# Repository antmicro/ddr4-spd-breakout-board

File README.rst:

=======================
DDR4 SPD Breakout Board
=======================

Copyright (c) 2022 `Antmicro <https://www.antmicro.com>`_

.. figure:: img/ddr4-spd-breakout.png

Overview
--------

This repository contains open hardware design files for an experimental breakout board which allows reading the Serial Presence Detect (SPD) data from a 288-pin, JEDEC-compliant DDR4 DIMM module.  

The board includes a FT2232HL USB/UART converter with MPSSE which can read DIMM-content over I2C.
This board can be used with our `SPD Data Reader <https://github.com/antmicro/spd-data-reader>`_ software.

Repository structure
--------------------
The main repository directory contains KiCad PCB project files, a LICENSE and README.
The remaining files are stored in the following directories:

* ``lib`` - contains the component libraries
* ``img`` - contains graphics for this README

License
=======

`Apache-2.0 <LICENSE>`_

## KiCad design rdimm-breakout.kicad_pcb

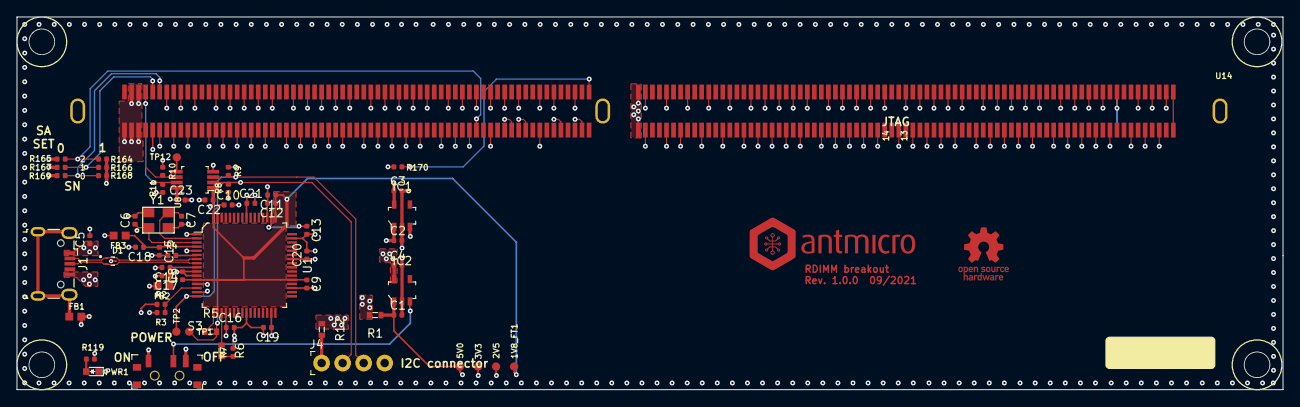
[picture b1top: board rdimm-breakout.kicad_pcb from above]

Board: 4 copper layers, 152.9 x 45.0 mm, 66 parts (0 on the bottom side), 34 nets.

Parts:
1V8_FT1, 2V5, 3V3, 5V0: TP_SMD1MM; Testpoint_smd_1mm
C1, C2, C3, C4: C_1u_0402; 0402-cap
C5, C8, C9, C10, C11, C13, C14, C15, C16, C19, C20, C21, C22, C23: C_100n_0402; 0402-cap
C6, C7: C_27p_0402; 0402-cap
C12, C17, C18: C_4u7_0402; 0402-cap
D1: PESD5V0S2BQA; TPD2E009DRTR
FB1, FB2, FB3: BLM18AG601SN1D; 0603
IC1: MIC5317-2.5YM5-TR; SOT-23-5
IC2: MIC5225-3.3YM5-TR; SOT-23-5
J1: WE_629105150521; USB_Micro_B_Female_629105150521
J4: 0022232041; PinHeader_1x4_P2.54mm_Drill1.02mm
N1: oshw_logo; oshw-logo
N2: antmicro_logo; antmicro-logo_scaled_20mm
PWR1: KP-1608CGCK; LED_0603
R1, R5, R6, R12: R_0R_0603; 0603-res
R2, R170: R_4k7_0402; 0402-res
R3, R8, R9, R10, R11: R_10k_0402; 0402-res
R4: R_12k_0402; 0402-res
R7: R_220R_0402; 0402-res
R119: R_330R_0402; 0402-res
R164, R165, R166, R167, R168, R169: R_0R_0402; 0402-res
S3: MSS3-V-T_R; Switch_Slide_MSS3
TP1, TP2, TP12: TP_SMD1MM; Testpoint_smd_1mm
U1: FT2232HL-REEL; LQFP-64_10x10mm
U8: PCA9517ADMR2G; TSSOP-8_W3mm
U14: 2199155-1
Y1: KX-7_12,MHz; KX-7

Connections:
1V8_FT: 1V8_FT1.1, C8.1, C9.1, C10.1, C11.1, C12.1, U1.12, U1.37, U1.49, U1.64
/FTDI/3V3_EN: IC2.3, S3.2
/FTDI/FTDI_RST: R2.2, R3.1, U1.14
/FTDI/USB_D_N: D1.1, J1.2, U1.7
/FTDI/USB_D_P: D1.2, J1.3, U1.8
GND: C1.2, C2.2, C3.2, C4.2, C5.2, C6.2, C7.2, C8.2, C9.2, C10.2, C11.2, C12.2, C13.2, C14.2, C15.2, C16.2, C17.2, C18.2, C19.2, C20.2, C21.2, C22.2, C23.2, D1.3, FB1.2, IC1.2, IC2.2, J1.5, J4.4, R3.2, R4.1, R7.2, R119.2, R165.2, R167.2, R169.2, S3.3, U1.1, U1.5, U1.10, U1.11, U1.13, U1.15, U1.25, U1.35, U1.47, U1.51, U8.4, U14.2, U14.4, U14.6, U14.9, U14.11, U14.13, U14.15, U14.17, U14.20, U14.22, U14.24, U14.26, U14.28, U14.31, U14.33, U14.35, U14.37, U14.39, U14.42, U14.44, U14.46, U14.48, U14.50, U14.53, U14.55, U14.57, U14.94, U14.96, U14.98, U14.101, U14.103, U14.105, U14.107, U14.109, U14.112, U14.114, U14.116, U14.118, U14.120, U14.123, U14.125, U14.127, U14.129, U14.131, U14.134, U14.136, U14.138, U14.147, U14.149, U14.151, U14.154, U14.156, U14.158, U14.160, U14.162, U14.165, U14.167, U14.169, U14.171, U14.173, U14.176, U14.178, U14.180, U14.182, U14.184, U14.187, U14.189, U14.191, U14.193, U14.195, U14.198, U14.200, U14.202, U14.204, U14.206, U14.209, U14.212, U14.215, U14.217, U14.220, U14.239, U14.241, U14.243, U14.246, U14.248, U14.250, U14.252, U14.254, U14.257, U14.259, U14.261, U14.263, U14.265, U14.268, U14.270, U14.272, U14.274, U14.276, U14.279, U14.281, U14.283, Y1.2, Y1.4
NC: U14.1, U14.145
unnamed: C14.1, C17.1, FB2.1, U1.9
unnamed: C15.1, C18.1, FB3.1, U1.4
unnamed: FB1.1, J1.6
unnamed: PWR1.2, R119.1
unnamed: R4.2, U1.6
unnamed: R5.1, U1.17
unnamed: R6.1, U1.19
unnamed: TP12.1, U8.5
OSCI: C7.1, U1.2, Y1.3
OSCO: C6.1, U1.3, Y1.1
SA0: R168.2, R169.1, U14.139
SA1: R166.2, R167.1, U14.140
SA2: R164.2, R165.1, U14.238
SCL: J4.2, R5.2, R8.2, TP1.1, U1.18, U8.2
SCL_2V5: R11.2, U8.7, U14.141
SDA: J4.3, R9.2, TP2.1, U1.16, U8.3
SDA_2V5: R10.2, U8.6, U14.285
VBUS: C5.1, J1.1, R1.2
VCC2V5: 2V5.1, C3.1, C23.1, IC1.5, R10.1, R11.1, R164.1, R166.1, R168.1, R170.1, U8.8, U14.284
VCC3V3: 3V3.1, C2.1, C4.1, C13.1, C16.1, C19.1, C20.1, C21.1, C22.1, FB2.2, FB3.2, IC1.1, IC1.3, IC2.5, PWR1.1, R2.1, R8.1, R9.1, R12.1, S3.1, U1.20, U1.31, U1.42, U1.50, U1.56, U8.1
VCC5V0: 5V0.1, C1.1, IC2.1, R1.1
VDDQ: U14.59, U14.61, U14.64, U14.67, U14.70, U14.73, U14.76, U14.80, U14.83, U14.85, U14.88, U14.90, U14.92, U14.223, U14.226, U14.229, U14.231, U14.233, U14.236
VPP: U14.142, U14.143, U14.286, U14.287, U14.288
VTT: U14.77, U14.221
V_AUX: J4.1, R12.2
WP: R6.2, R7.1
~EVENT: R170.2, U14.78

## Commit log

2022-04-14 Add schematics - initial commit
2022-04-14 Add LICENSE
2022-04-14 Add initial PCB design
2022-04-14 Fix 3V3 EN signal - bump rev. to 1.0.2
2022-04-14 Update naming convention
2022-04-14 Clean up designators
2022-04-14 Add 3D view to the schematic
2022-04-14 Add FTDI and USB power supply
2022-04-14 Add layout
2022-04-14 Replace 3D view on schematic
2022-04-14 Bump rev to 1.0.1
2022-04-14 Add initial component placement
2022-04-14 Update labels on the schematics
2022-04-14 Annotate components
2022-04-14 Assign MPN to the RDIMM connector
2022-04-14 Add I2C connector
2022-04-14 Replace LDO
2022-04-14 Fix EC-DRC errors
2022-04-14 Add README
2022-04-14 README: Update photo
